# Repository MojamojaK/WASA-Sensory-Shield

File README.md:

# WASA-Sensory-Shield
Kicad Sensory Shield for WASA HPA project

回路設計はマイケル
基板設計は後輩がやってくれました

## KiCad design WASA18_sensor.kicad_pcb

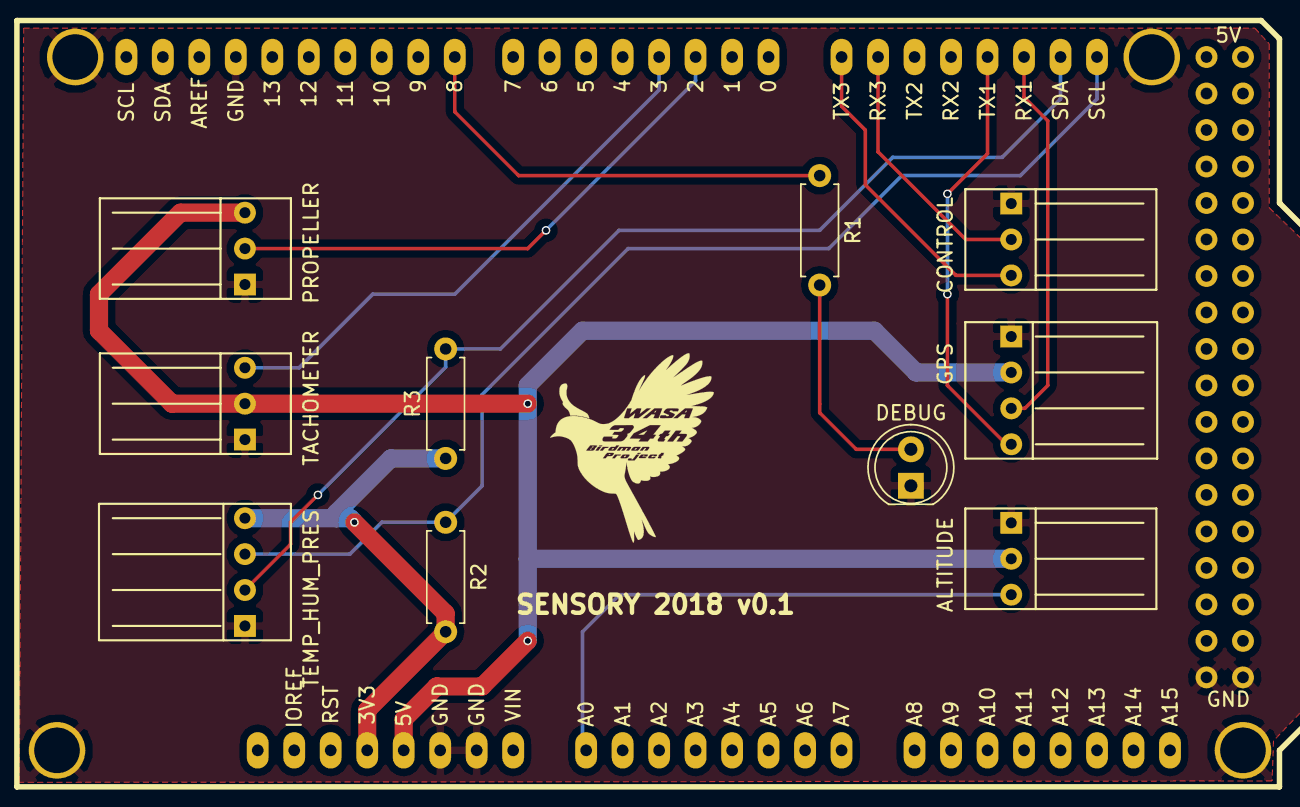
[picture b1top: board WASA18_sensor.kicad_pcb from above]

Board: 2 copper layers, 11 parts (0 on the bottom side), 14 nets.

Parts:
ALTITUDE: ALTITUDE; Molex-5046-P2.50mm-0x03
CONTROL: CONTROL; Molex-5046-P2.50mm-0x03
DEBUG: LED; LED_D5.0mm
GPS: GPS_MOUSE; Molex-5046-P2.50mm-0x04
PROPELLER: PROPELLER; Molex-5046-P2.50mm-0x03
R1: 1K; R_Axial_DIN0207_L6.3mm_D2.5mm_P7.62mm_Horizontal
R2, R3: 10K; R_Axial_DIN0207_L6.3mm_D2.5mm_P7.62mm_Horizontal
SENSORY 2018 v0.1: ARDUINO_MEGA_SHIELD; ARDUINO_MEGA_SHIELD_R3_94.49x53.34
TACHOMETER: TACHOMETER; Molex-5046-P2.50mm-0x03
TEMP_HUM_PRES: TEMP_HUM_PRES; Molex-5046-P2.50mm-0x04

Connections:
3V3: R2.2, R3.1, SENSORY 2018 v0.1.3V3, TEMP_HUM_PRES.4
5V: ALTITUDE.2, GPS.2, PROPELLER.3, SENSORY 2018 v0.1.5V, TACHOMETER.2
ALTI_SIG: ALTITUDE.3, SENSORY 2018 v0.1.AD0
CONTROL_RX: CONTROL.2, SENSORY 2018 v0.1.15
CONTROL_TX: CONTROL.3, SENSORY 2018 v0.1.14
DEBUG_LED: R1.1, SENSORY 2018 v0.1.8
GND: ALTITUDE.1, CONTROL.1, DEBUG.1, GPS.1, PROPELLER.1, SENSORY 2018 v0.1.GND1, SENSORY 2018 v0.1.GND2, SENSORY 2018 v0.1.GND3, SENSORY 2018 v0.1.GND4, SENSORY 2018 v0.1.GND5, TACHOMETER.1, TEMP_HUM_PRES.1
GPS_RX: GPS.3, SENSORY 2018 v0.1.19
GPS_TX: GPS.4, SENSORY 2018 v0.1.18
unnamed: DEBUG.2, R1.2
PROP: PROPELLER.2, SENSORY 2018 v0.1.2
SCL: R2.1, SENSORY 2018 v0.1.21, TEMP_HUM_PRES.3
SDA: R3.2, SENSORY 2018 v0.1.20, TEMP_HUM_PRES.2
TACH: SENSORY 2018 v0.1.3, TACHOMETER.3

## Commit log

2018-03-03 Updated to match .gitignore
2018-03-03 Create LICENSE
